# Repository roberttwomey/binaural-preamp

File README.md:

# binaural-preamp
binaural microphone preamp for stereo electrets using tl072 opamp

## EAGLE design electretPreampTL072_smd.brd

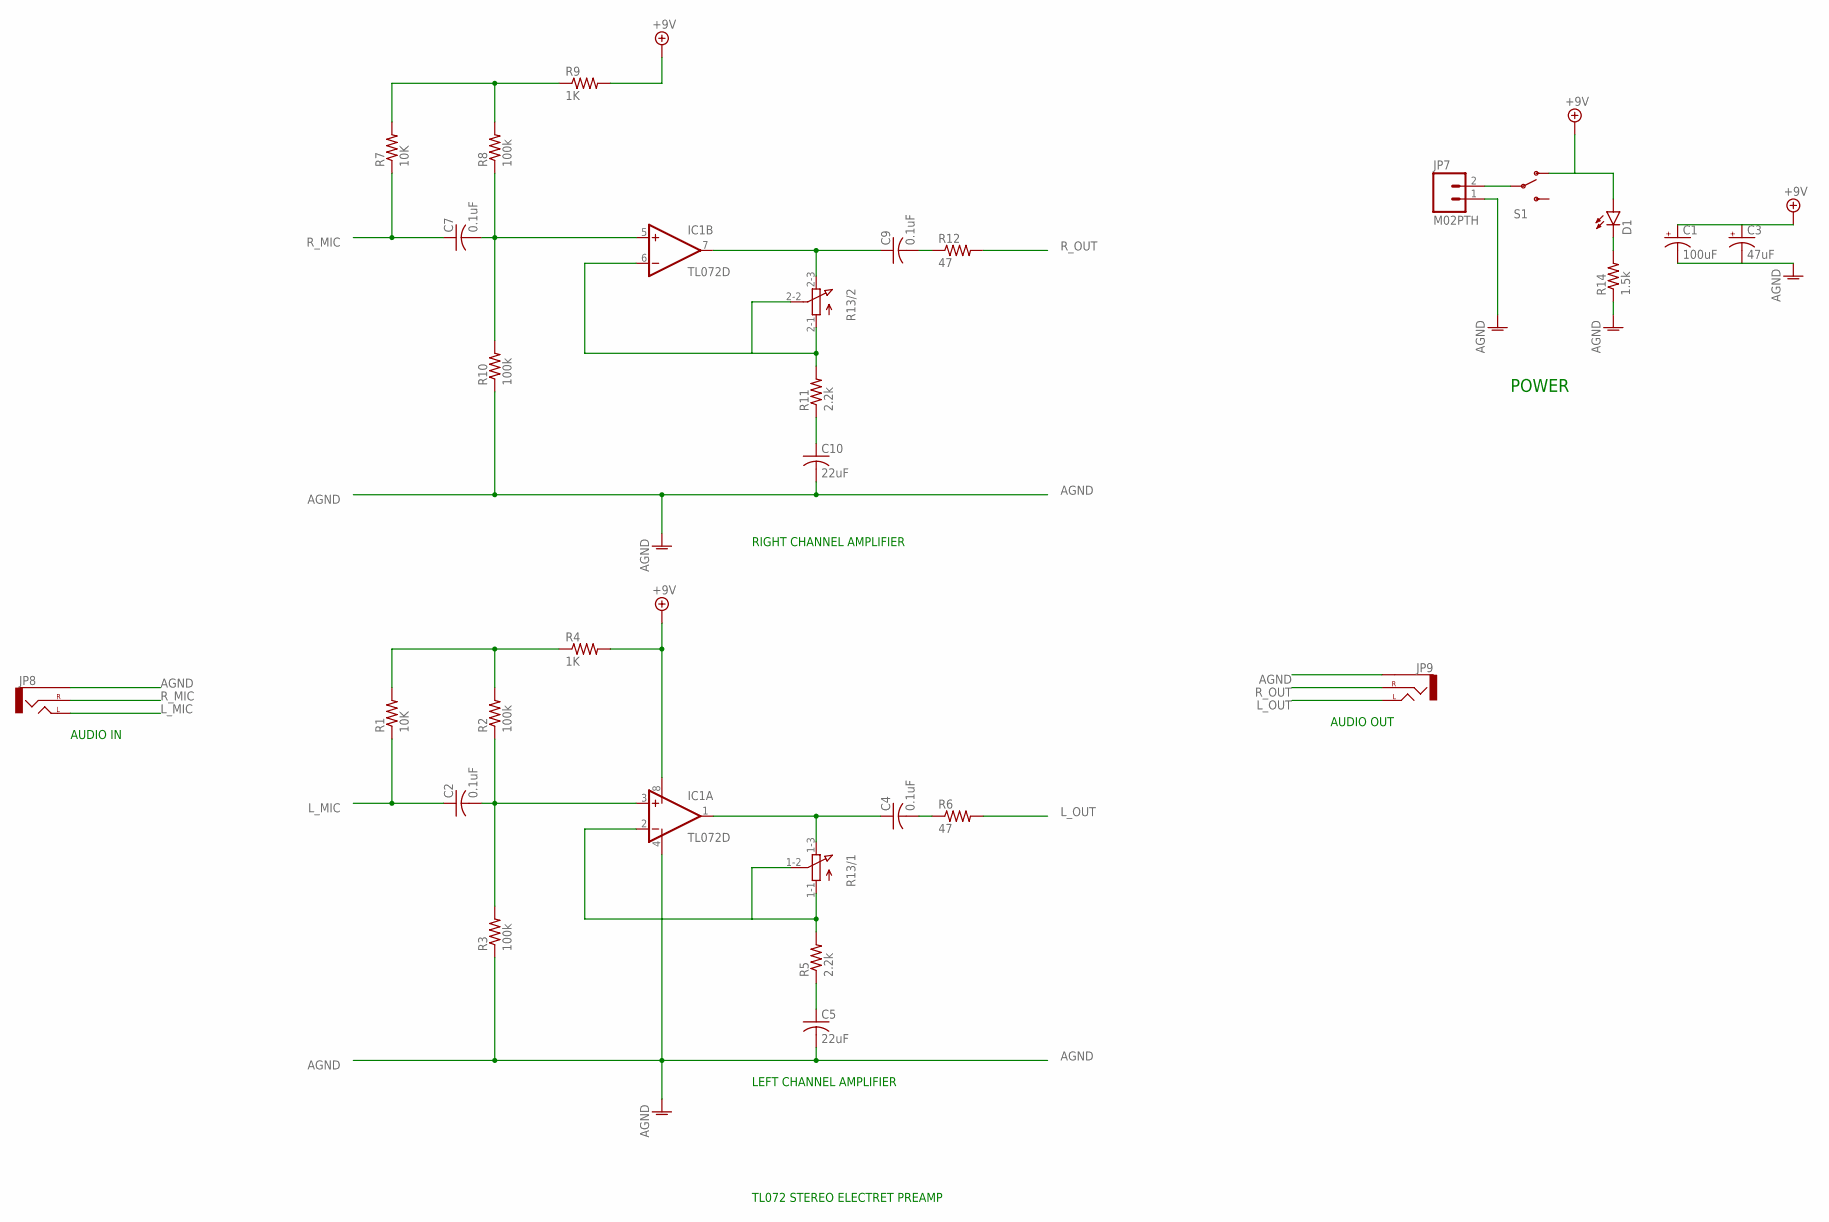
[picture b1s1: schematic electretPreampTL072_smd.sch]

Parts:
C1: 100uF; PANASONIC_D
C2, C4, C7, C9: 0.1uF; C0603
C3: 47uF; PANASONIC_D
C5, C10: 22uF; C0603
D1: LED0603; LED-0603
IC1: TL072D; SO08
JP7: M02PTH; 1X02
JP8, JP9: AUDIO-JACKSMD2; AUDIO-JACK-3.5MM-SMD
R1, R7: 10K; 0603-RES
R2, R3, R8, R10: 100k; 0603-RES
R4, R9: 1K; 0603-RES
R5, R11: 2.2k; 0603-RES
R6, R12: 47; 0603-RES
R13: 3RP/1610G; RK097122008T
R14: 1.5k; 0603-RES
S1: SWITCH-SPDTPTH; SWITCH-SPDT

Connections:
+9V: D1.A, IC1.8 (V+), R4.2, R9.2, S1.1 (O)
AGND: C1.-, C3.-, C5.2, C10.2, IC1.4 (V-), JP7.1, JP8.SLEEVE, JP9.SLEEVE, R3.1, R10.1, R14.1
BATT+: C1.+, C3.+, JP7.2, S1.2
L_MIC: C2.1, JP8.TIP (LEFT), R1.1
L_OUT: JP9.TIP (LEFT), R6.2
L_OUT_PRE: C4.1, IC1.1 (OUT), R13.1-3 (E)
unnamed: D1.C, R14.2
unnamed: C4.2, R6.1
unnamed: IC1.2 (-IN), R5.2, R13.1-1 (A), R13.1-2 (S)
unnamed: C5.1, R5.1
unnamed: C2.2, IC1.3 (+IN), R2.1, R3.2
unnamed: C9.2, R12.1
unnamed: R1.2, R2.2, R4.1
unnamed: IC1.6 (-IN), R11.2, R13.2-1 (A), R13.2-2 (S)
unnamed: C10.1, R11.1
unnamed: C7.2, IC1.5 (+IN), R8.1, R10.2
unnamed: R7.2, R8.2, R9.1
R_MIC: C7.1, JP8.RING (RIGHT), R7.1
R_OUT: JP9.RING (RIGHT), R12.2
R_OUT_PRE: C9.1, IC1.7 (OUT), R13.2-3 (E)

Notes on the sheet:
TL072 STEREO ELECTRET PREAMP
RIGHT CHANNEL AMPLIFIER
AUDIO OUT
LEFT CHANNEL AMPLIFIER
AUDIO IN
POWER

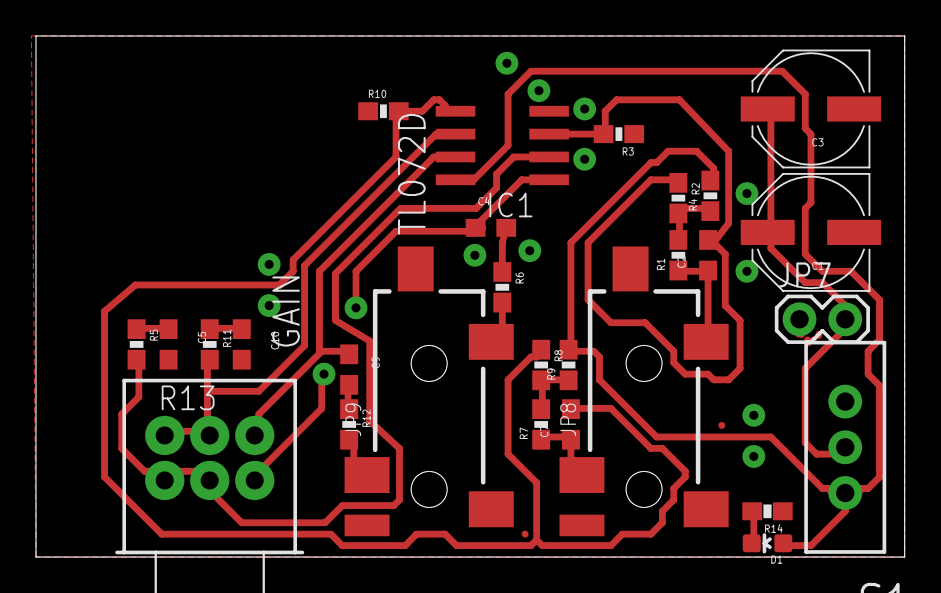
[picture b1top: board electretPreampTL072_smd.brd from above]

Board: 2 copper layers, 48.3 x 28.9 mm, 28 parts (0 on the bottom side), 20 nets.

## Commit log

2017-01-04 added enclosure files
2017-01-13 started enclosure model

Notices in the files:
parts and their libraries:
SparkFun-Resistors: Licensing: CC v3.0 Share-Alike You are welcome to use this library for commercial purposes.
SparkFun-Connectors: Licensing: Creative Commons ShareAlike 4.0 International - https://creativecommons.org/licenses/by-sa/4.0
